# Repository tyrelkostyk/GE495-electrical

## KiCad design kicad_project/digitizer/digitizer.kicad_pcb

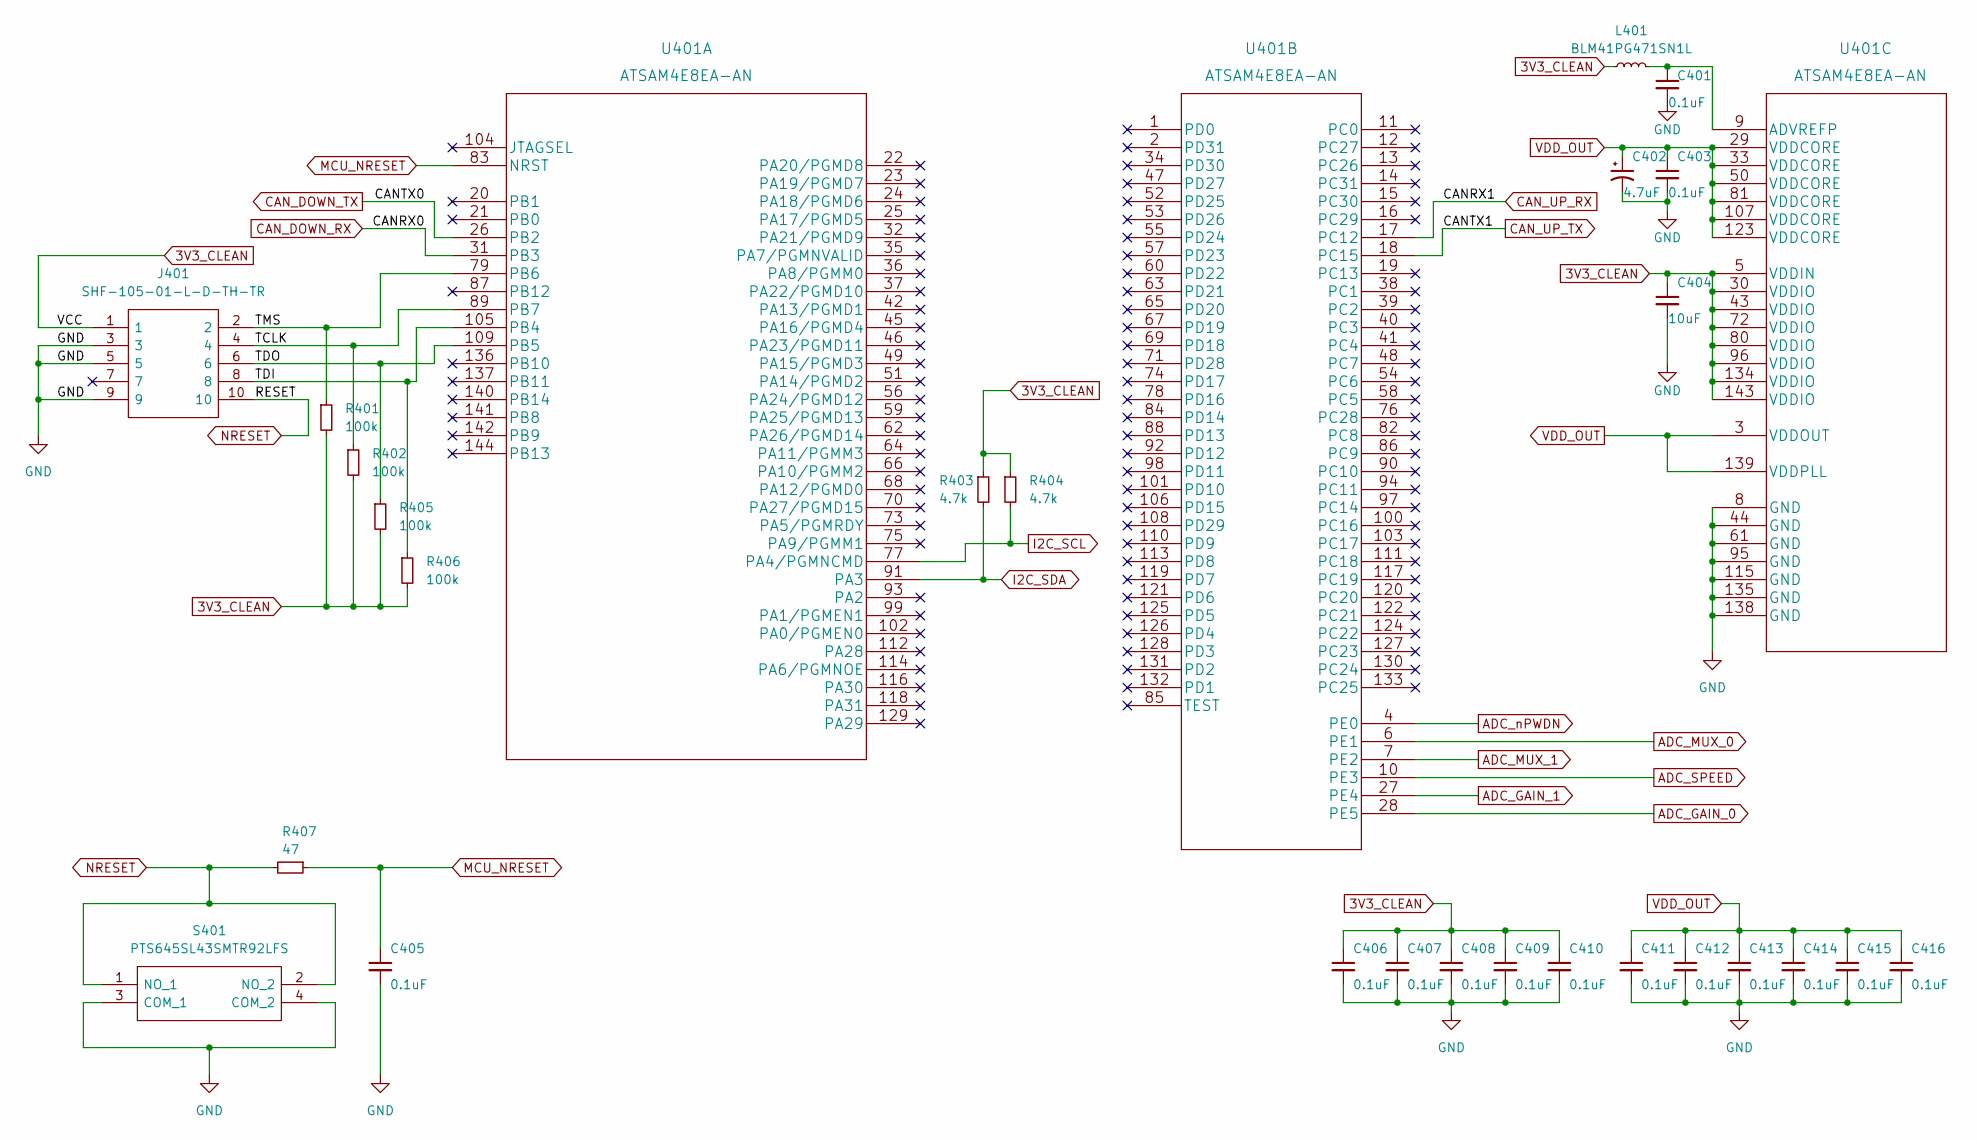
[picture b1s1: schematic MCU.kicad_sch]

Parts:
C401, C403, C405, C406, C407, C408, C409, C410, C411, C412, C413, C414, C415, C416: 0.1uF; C_0805_2012Metric_Pad1.18x1.45mm_HandSolder
C402: 4.7uF; C_0805_2012Metric_Pad1.18x1.45mm_HandSolder
C404: 10uF; C_0805_2012Metric_Pad1.18x1.45mm_HandSolder
J401: SHF-105-01-L-D-TH-TR; SHF10501LDTHTR; Mouser Part Number 200-SHF10501LDTHTR
L401: BLM41PG471SN1L; L_1806_4516Metric_Pad1.45x1.90mm_HandSolder
R401, R402, R405, R406: 100k; R_0805_2012Metric_Pad1.20x1.40mm_HandSolder
R403, R404: 4.7k; R_0805_2012Metric_Pad1.20x1.40mm_HandSolder
R407: 47; R_0805_2012Metric_Pad1.20x1.40mm_HandSolder
S401: PTS645SL43SMTR92LFS; Mouser Part Number 611-PTS645SL43SMTR92
U401: ATSAM4E8EA-AN

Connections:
3V3_CLEAN: C404.1, C406.1, C407.1, C408.1, C409.1, C410.1, J401.1, L401.1, R401.2, R402.2, R403.1, R404.1, R405.2, R406.2, U401.5 (VDDIN), U401.30 (VDDIO), U401.43 (VDDIO), U401.72 (VDDIO), U401.80 (VDDIO), U401.96 (VDDIO), U401.134 (VDDIO), U401.143 (VDDIO); also elsewhere on the board
/MCU/TCLK: J401.4, R402.1, U401.89 (PB7)
/MCU/TDI: J401.8, R406.1, U401.105 (PB4)
/MCU/TDO: J401.6, R405.1, U401.109 (PB5)
/MCU/TMS: J401.2, R401.1, U401.79 (PB6)
ADC_GAIN_0: U401.28 (PE5); also elsewhere on the board
ADC_GAIN_1: U401.27 (PE4); also elsewhere on the board
ADC_MUX_0: U401.6 (PE1); also elsewhere on the board
ADC_MUX_1: U401.7 (PE2); also elsewhere on the board
ADC_SPEED: U401.10 (PE3); also elsewhere on the board
ADC_nPWDN: U401.4 (PE0); also elsewhere on the board
CAN_DOWN_RX: U401.31 (PB3); also elsewhere on the board
CAN_DOWN_TX: U401.26 (PB2); also elsewhere on the board
CAN_UP_RX: U401.17 (PC12); also elsewhere on the board
CAN_UP_TX: U401.18 (PC15); also elsewhere on the board
GND: C401.2, C402.2, C403.2, C404.2, C405.2, C406.2, C407.2, C408.2, C409.2, C410.2, C411.2, C412.2, C413.2, C414.2, C415.2, C416.2, J401.3, J401.5, J401.9, S401.3 (COM_1), S401.4 (COM_2), U401.8 (GND), U401.44 (GND), U401.61 (GND), U401.95 (GND), U401.115 (GND), U401.135 (GND), U401.138 (GND); also elsewhere on the board
I2C_SCL: R404.2, U401.77 (PA4/PGMNCMD); also elsewhere on the board
I2C_SDA: R403.2, U401.91 (PA3); also elsewhere on the board
MCU_NRESET: C405.1, R407.1, U401.83 (NRST)
NRESET: J401.10, R407.2, S401.1 (NO_1), S401.2 (NO_2)
unnamed: C401.1, L401.2, U401.9 (ADVREFP)
VDD_OUT: C402.1, C403.1, C411.1, C412.1, C413.1, C414.1, C415.1, C416.1, U401.3 (VDDOUT), U401.29 (VDDCORE), U401.33 (VDDCORE), U401.50 (VDDCORE), U401.81 (VDDCORE), U401.107 (VDDCORE), U401.123 (VDDCORE), U401.139 (VDDPLL)

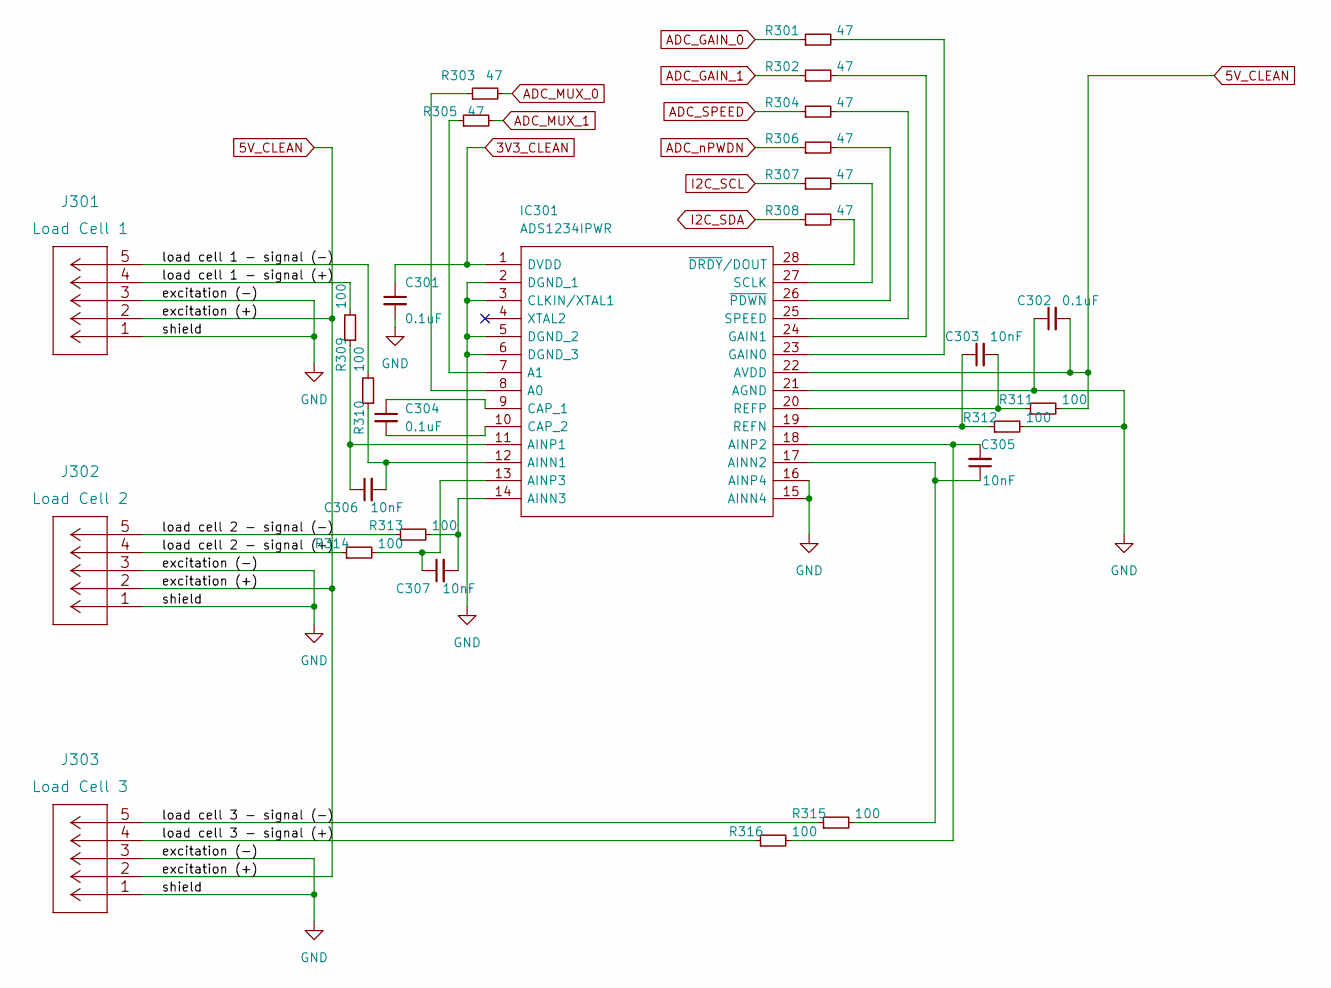
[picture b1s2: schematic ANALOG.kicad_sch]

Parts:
C301, C302, C304: 0.1uF; C_0805_2012Metric_Pad1.18x1.45mm_HandSolder
C303, C305, C306, C307: 10nF; C_0805_2012Metric_Pad1.18x1.45mm_HandSolder
IC301: ADS1234IPWR; SOP65P640X120-28N; Mouser Part Number 595-ADS1234IPWR
J301: Load Cell 1; 1935190
J302: Load Cell 2; 1935190
J303: Load Cell 3; 1935190
R301, R302, R303, R304, R305, R306, R307, R308: 47; R_0805_2012Metric_Pad1.20x1.40mm_HandSolder
R309, R310, R311, R312, R313, R314, R315, R316: 100; R_0805_2012Metric_Pad1.20x1.40mm_HandSolder

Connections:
3V3_CLEAN: C301.1, IC301.1 (DVDD); also elsewhere on the board
5V_CLEAN: C302.2, IC301.22 (AVDD), J301.2, J302.2, J303.2, R311.2; also elsewhere on the board
/ANALOG/load cell 1 - signal (+): J301.4, R309.2
/ANALOG/load cell 1 - signal (-): J301.5, R310.2
/ANALOG/load cell 2 - signal (+): J302.4, R314.1
/ANALOG/load cell 2 - signal (-): J302.5, R313.1
/ANALOG/load cell 3 - signal (+): J303.4, R316.1
/ANALOG/load cell 3 - signal (-): J303.5, R315.1
ADC_GAIN_0: R301.1; also elsewhere on the board
ADC_GAIN_1: R302.1; also elsewhere on the board
ADC_MUX_0: R303.2; also elsewhere on the board
ADC_MUX_1: R305.2; also elsewhere on the board
ADC_SPEED: R304.1; also elsewhere on the board
ADC_nPWDN: R306.1; also elsewhere on the board
GND: C301.2, C302.1, IC301.2 (DGND_1), IC301.3 (CLKIN/XTAL1), IC301.5 (DGND_2), IC301.6 (DGND_3), IC301.15 (AINN4), IC301.16 (AINP4), IC301.21 (AGND), J301.1, J301.3, J302.1, J302.3, J303.1, J303.3, R312.2; also elsewhere on the board
I2C_SCL: R307.1; also elsewhere on the board
I2C_SDA: R308.1; also elsewhere on the board
unnamed: C303.1, IC301.19 (REFN), R312.1
unnamed: C303.2, IC301.20 (REFP), R311.1
unnamed: C304.1, IC301.9 (CAP_1)
unnamed: C304.2, IC301.10 (CAP_2)
unnamed: C305.1, IC301.17 (AINN2), R315.2
unnamed: C305.2, IC301.18 (AINP2), R316.2
unnamed: C306.1, IC301.11 (AINP1), R309.1
unnamed: C306.2, IC301.12 (AINN1), R310.1
unnamed: C307.1, IC301.13 (AINP3), R314.2
unnamed: C307.2, IC301.14 (AINN3), R313.2
unnamed: IC301.7 (A1), R305.1
unnamed: IC301.8 (A0), R303.1
unnamed: IC301.23 (GAIN0), R301.2
unnamed: IC301.24 (GAIN1), R302.2
unnamed: IC301.25 (SPEED), R304.2
unnamed: IC301.26 (~PDWN), R306.2
unnamed: IC301.27 (SCLK), R307.2
unnamed: IC301.28 (~DRDY/DOUT), R308.2

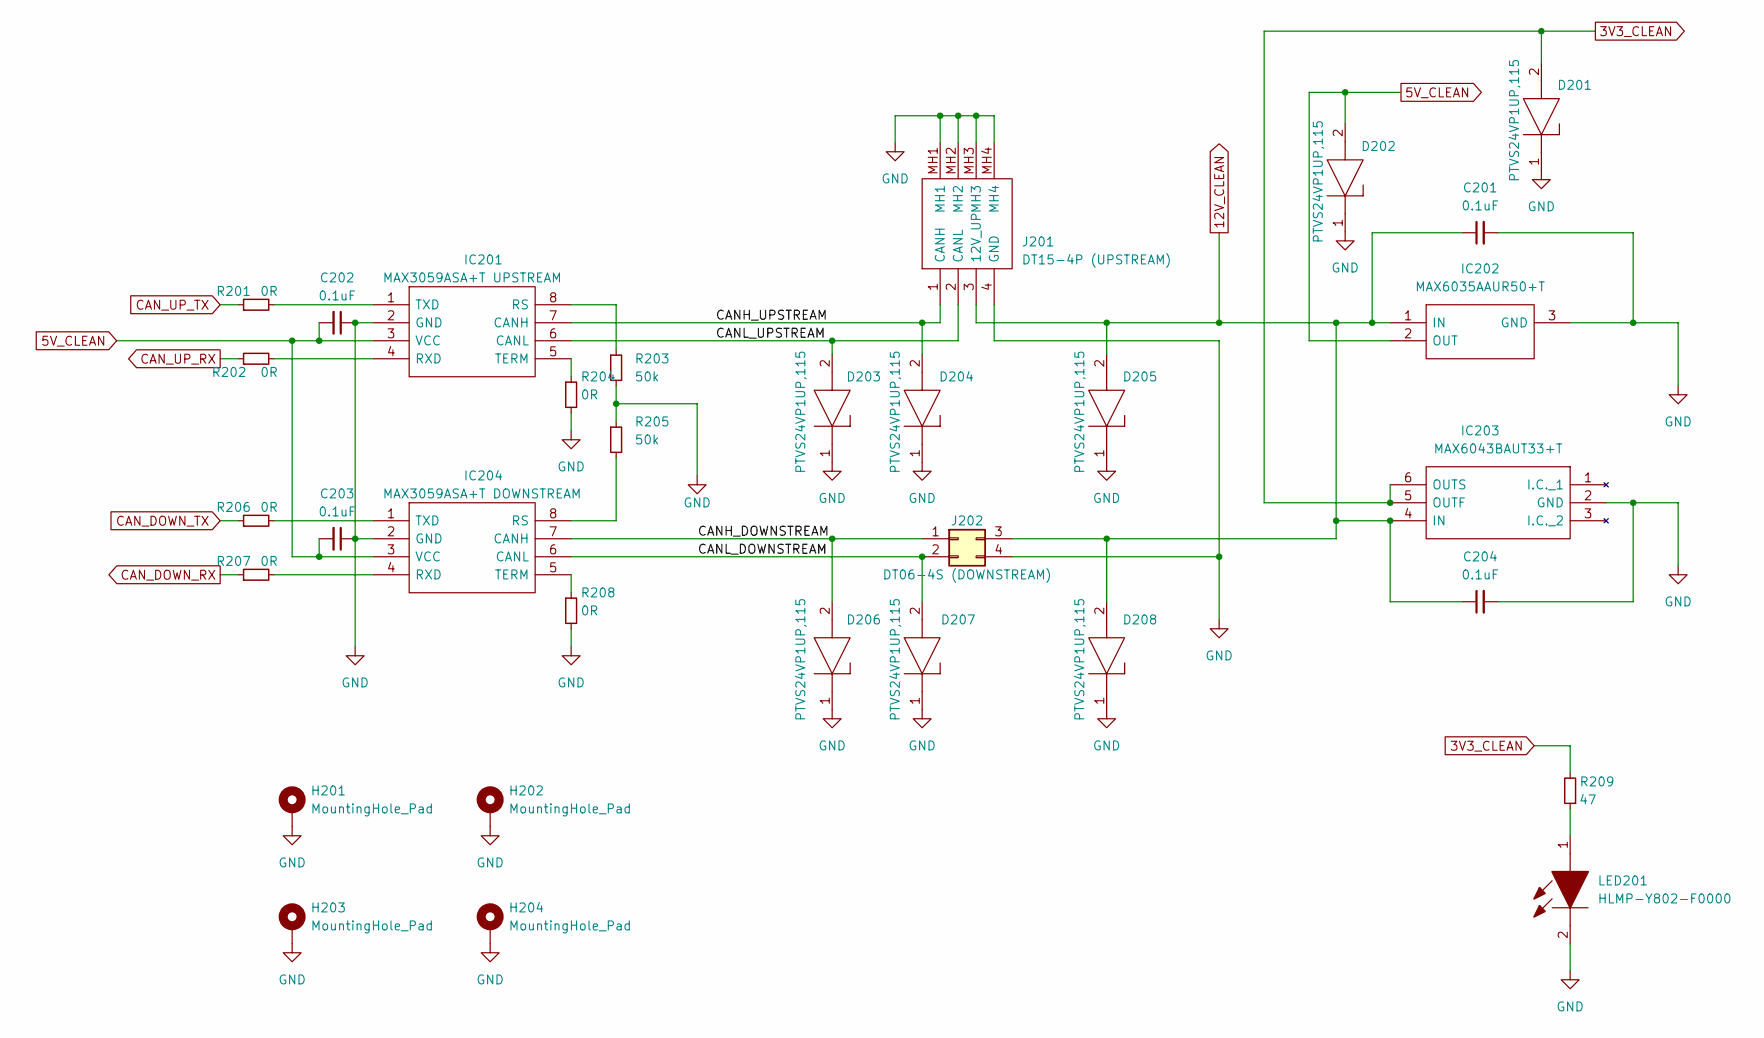
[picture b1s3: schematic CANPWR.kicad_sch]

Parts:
C201, C202, C203, C204: 0.1uF; C_0805_2012Metric_Pad1.18x1.45mm_HandSolder
D201, D202, D203, D204, D205, D206, D207, D208: PTVS24VP1UP,115; PMEG3050EP115; Mouser Part Number 771-PTVS24VP1UP115
H201, H202, H203, H204: MountingHole_Pad; MountingHole_3.2mm_M3_Pad
IC201: MAX3059ASA+T UPSTREAM; SOIC127P600X175-8N; Mouser Part Number 700-MAX3059ASAT
IC202: MAX6035AAUR50+T; SOT95P237X112-3N; Manufacturer_Part_Number MAX6035AAUR50+T
IC203: MAX6043BAUT33+T; SOT95P280X145-6N; Mouser Part Number 700-MAX6043BAUT33+T
IC204: MAX3059ASA+T DOWNSTREAM; SOIC127P600X175-8N; Mouser Part Number 700-MAX3059ASAT
J201: DT15-4P (UPSTREAM); DT154P; Mouser Part Number 571-DT15-4P
J202: DT06-4S (DOWNSTREAM); 1935187
LED201: HLMP-Y802-F0000; HLMPY802F0000; Mouser Part Number 630-HLMP-Y802-F0000
R201, R202, R204, R206, R207, R208: 0R; R_0805_2012Metric_Pad1.20x1.40mm_HandSolder
R203, R205: 50k; R_0805_2012Metric_Pad1.20x1.40mm_HandSolder
R209: 47; R_0805_2012Metric_Pad1.20x1.40mm_HandSolder

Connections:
3V3_CLEAN: D201.2, IC203.5 (OUTF), IC203.6 (OUTS), R209.2; also elsewhere on the board
5V_CLEAN: C202.2, C203.2, D202.2, IC201.3 (VCC), IC202.2 (OUT), IC204.3 (VCC); also elsewhere on the board
12V_CLEAN: C201.1, C204.1, D205.2, D208.2, IC202.1 (IN), IC203.4 (IN), J201.3 (12V_UP), J202.3 (12V_DOWN)
/CANPWR/CANH_DOWNSTREAM: D206.2, IC204.7 (CANH), J202.1 (CAN1)
/CANPWR/CANH_UPSTREAM: D204.2, IC201.7 (CANH), J201.1 (CANH)
/CANPWR/CANL_DOWNSTREAM: D207.2, IC204.6 (CANL), J202.2 (CANL)
/CANPWR/CANL_UPSTREAM: D203.2, IC201.6 (CANL), J201.2 (CANL)
CAN_DOWN_RX: R207.1; also elsewhere on the board
CAN_DOWN_TX: R206.1; also elsewhere on the board
CAN_UP_RX: R202.1; also elsewhere on the board
CAN_UP_TX: R201.1; also elsewhere on the board
GND: C201.2, C202.1, C203.1, C204.2, D201.1, D202.1, D203.1, D204.1, D205.1, D206.1, D207.1, D208.1, H201.1, H202.1, H203.1, H204.1, IC201.2 (GND), IC202.3 (GND), IC203.2 (GND), IC204.2 (GND), J201.4 (GND), J201.MH1, J201.MH2, J201.MH3, J201.MH4, J202.4 (GND), LED201.2, R203.2, R204.2, R205.1, R208.2; also elsewhere on the board
unnamed: IC201.1 (TXD), R201.2
unnamed: IC201.4 (RXD), R202.2
unnamed: IC201.5 (TERM), R204.1
unnamed: IC201.8 (RS), R203.1
unnamed: IC204.1 (TXD), R206.2
unnamed: IC204.4 (RXD), R207.2
unnamed: IC204.5 (TERM), R208.1
unnamed: IC204.8 (RS), R205.2
unnamed: LED201.1, R209.1

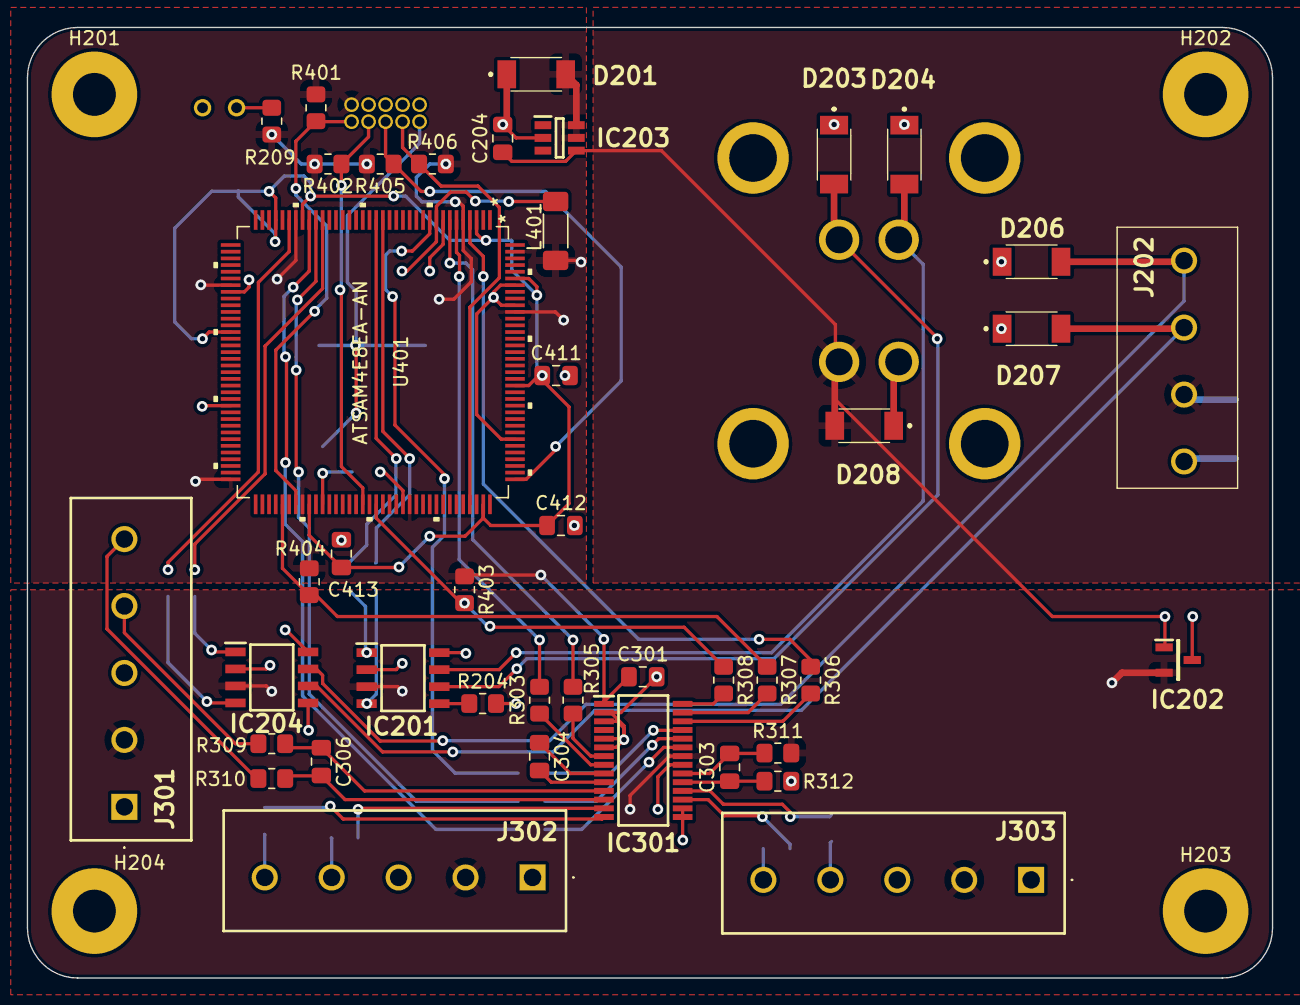
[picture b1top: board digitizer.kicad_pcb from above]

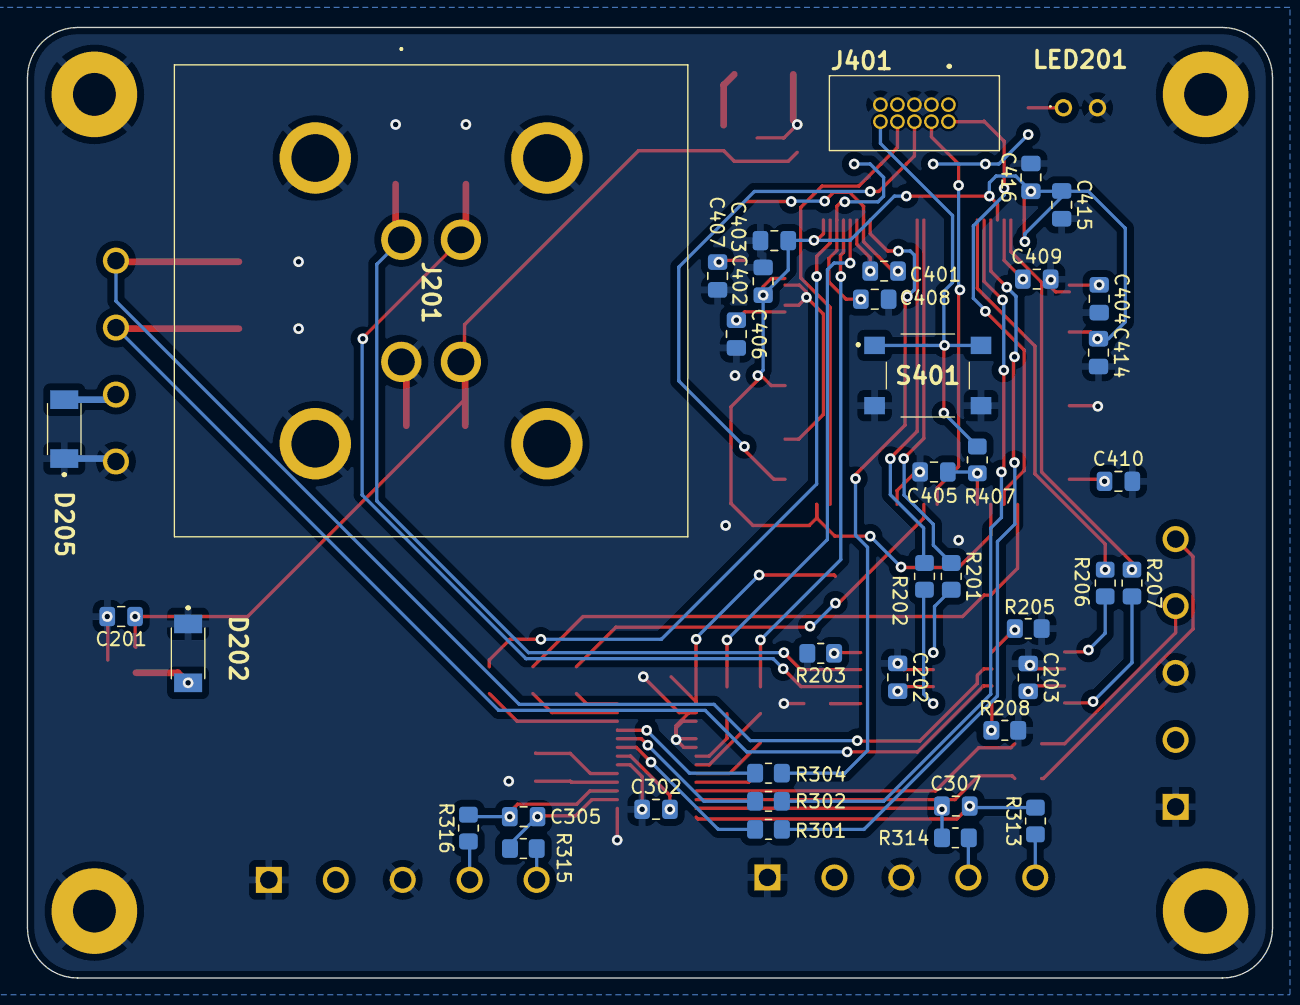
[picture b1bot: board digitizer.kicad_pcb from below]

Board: 2 copper layers, 93.0 x 71.0 mm, 86 parts (40 on the bottom side), 61 nets.

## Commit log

2022-01-15 created project; not sure if certain files should be ignored or included
2022-01-15 created footprint and symbol project library for our project; started work on the new symbol
2022-01-16 finished schematic symbol for the LPC1813JBD144, and connected it to the LQFP144 footprint! Placed it into the schematic
2022-01-16 updated gitignore to ignore backup files
2022-01-16 divided schematic up into 3 sheets, and placed the corresponding components within them. Have not connected anything or match the correct connectors to the proper footprints yet
2022-01-17 finished the CANPWR sheet, got to work on the MCU sheet (finished the CAN stuff). Good progress; still missing the MCU pin connections and the connector footprints (M12, deutsch, etc.)
2022-01-20 imported the correct symbols & footprints, and added a few to the schematic: pulled in the correct MCU symbol/footprint, as well as the correct JTAG footprint (connected to the 2x5 odd_even connector)
2022-01-28 moved CAN modules to the CANPWR sheet. Finished (first draft) of the MCU power design
2022-01-28 updated annotations
2022-01-28 added global flags to connect the MCU CAN lines with the CAN Transceivers
2022-01-28 connected the ADC I2C lines
2022-01-29 added the JTAG and Reset circuitry
2022-01-30 fixed the reset switch circuitry, added labels to CAN lines
2022-01-31 added GPIO lines, LED, other small changes
2022-01-31 added proper connector symbols and footprints for M12 and DT15 (digital upstream) connectors
2022-02-13 updated schematic to include terminal blocks for the analog M12 connectors and the downstream CANPWR connector
2022-02-14 cleared ALL errors from electrical rules check; had to explicitly define a bunch of pins, and remove a few bugs (shorted lines, etc.)
2022-02-14 removed unneccesary no-connects
2022-02-14 fixed another small bug; looks good to begin the board layout!
2022-02-14 updated a name
2022-02-14 created edge layer! Was harder than expected haha
2022-02-14 re-did the edges for the PCB; now has the correct radius of curvature for the corners (3.75mm)
2022-02-14 placed deutsch connector and 1 mounting hole; the former at the exact spot according to Isaac's specs, and the second at a slightly custom spot (see discord #mechanical channel for details)
2022-02-14 placed the rest of the mounting holes at my chosen location (each hole is 5mm from each x/y edge)
2022-02-14 placed all of the connectors and ICs in their initial spots/sides
2022-02-14 added a ground plane
2022-02-14 added 5pin term blocks for the M12 connections, so we can properly ground the shield connections
2022-02-14 added plane for 5V clean on the F.Cu layer
2022-02-14 added 12V_CLEAN label to schematic; added planes for 12V_CLEAN and 3V3_CLEAN to layout
2022-02-14 updated copper zones to properly connect to tiny solder pads
2022-02-14 placed & routed bypass capacitors for both power regulators
2022-02-14 routed LED connections; replaced 12V_CLEAN copper zone so it was one consecutive zone instead of 2 separate zones
2022-02-14 moved a few things around
2022-02-14 finished ADC routing, including MCU pins (MUX, I2C, etc.)
2022-02-15 backup commit; going to change all of the capacitor and resistor sizes to be much smaller
2022-02-15 updated schematic to use all 0805 parts (both caps and resistors)
2022-02-15 updated layout with new, smaller passive components
2022-02-15 continued layout progress; connected JTAG connector and reset switch, among a few other changes
2022-02-15 more progress! CAN ICs are done, just the MCU Power decoupling is left
2022-02-15 modified the power planes so that the 12V plane routes above the 3V3 plane, not below it (thus making the space below the MCU less crowded). Also completed some further connections
2022-02-15 progress on connecting PWR/GND pins
2022-02-15 more progress; finished connecting all passives and components except for MCU power pins
2022-02-15 added 100ohm resistors to the differential analog inputs
2022-02-15 finished GND (i think) and VDDCORE/VDDOUT pins
2022-02-15 placed all of the components!
2022-02-15 some refinements, fixed a few missing connections
2022-02-15 properly added mounting holes, drew proper dimension lines
2022-02-15 resolved all errors and warnings (ran DRC) for the PCB Layout
2022-02-15 cleaned up a few more things
2022-02-15 generated output fab files
2022-02-16 generated gerbers (put in ZIP), generated STEP file
2022-02-16 moved downstream connector to other side of board; flipped other connectors so they're easier to use; generated new .STEP file
2022-02-17 added some 0R resistors to pads to allow for easier board modding
2022-02-17 added TVS diodes to upstream and downstream connector signals
2022-02-17 added TVS diodes to 3V3 and 5V rails as well
2022-02-17 fixed everything up
2022-02-17 re-generated STEP file
2022-02-17 updated output files
2022-03-09 saved output files

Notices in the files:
parts and their libraries:
Copyright 2021 Accelerated Designs. All rights reserved.
